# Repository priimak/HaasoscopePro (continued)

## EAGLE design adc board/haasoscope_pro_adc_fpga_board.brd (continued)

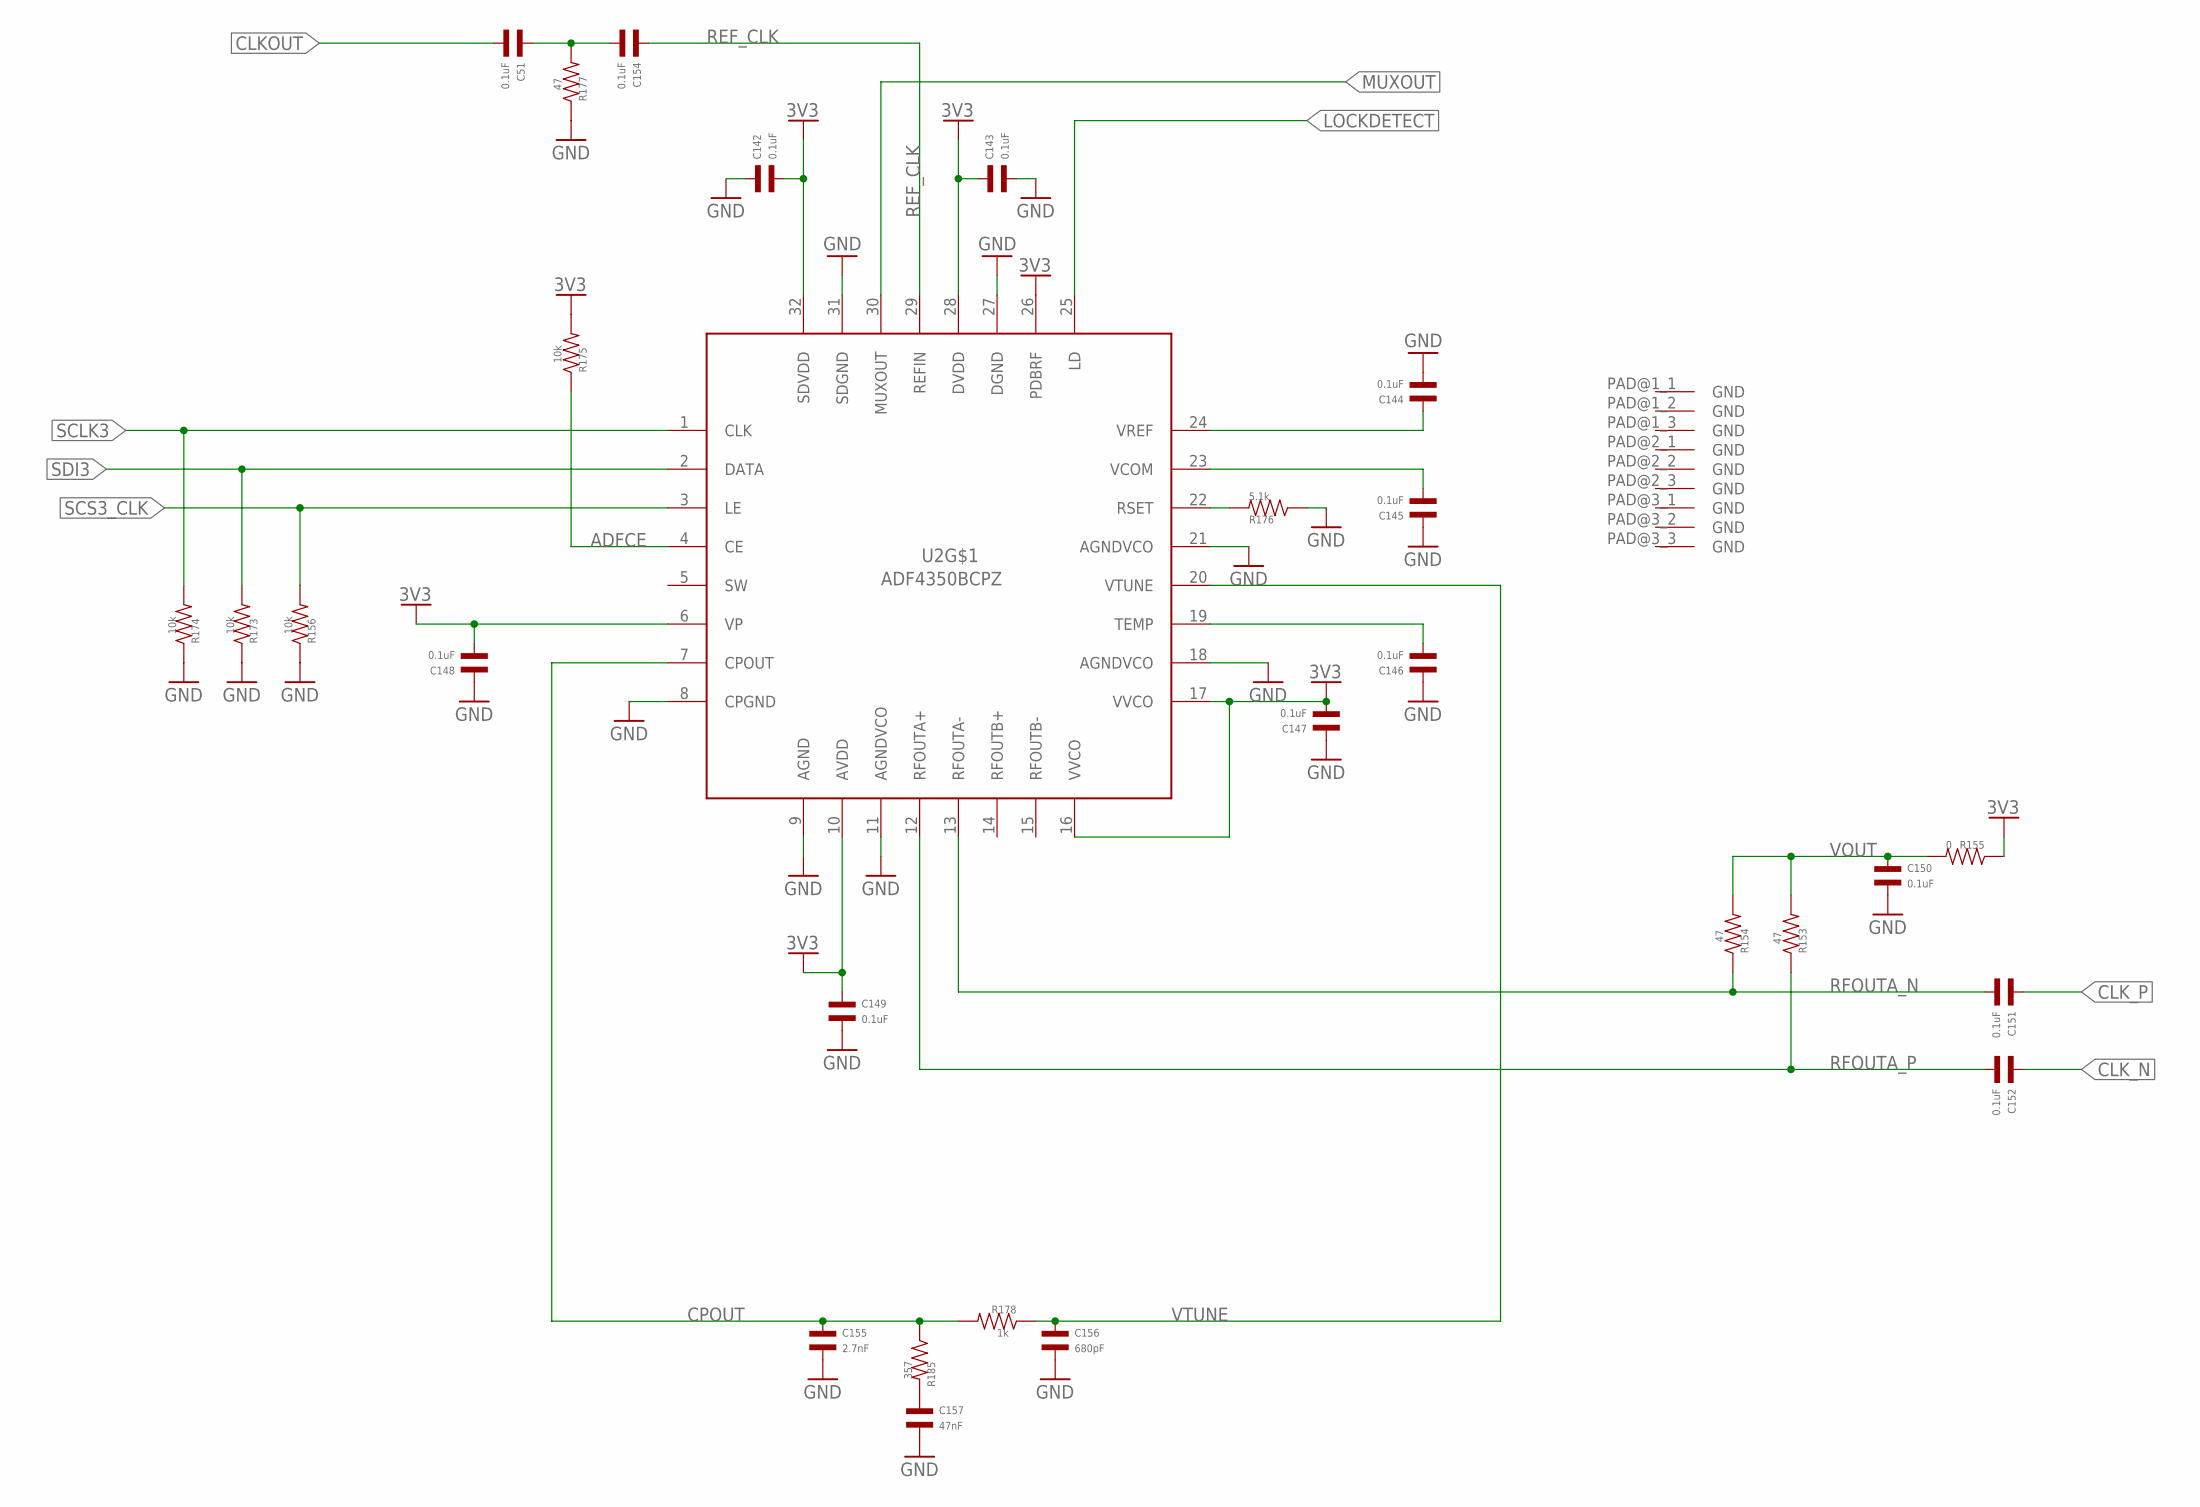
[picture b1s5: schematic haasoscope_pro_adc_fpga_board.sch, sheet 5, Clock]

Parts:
C51, C142, C143, C144, C145, C146, C147, C148, C149, C150, C151, C152, C154: 0.1uF; C0402
C155: 2.7nF; C0402
C156: 680pF; C0402
C157: 47nF; C0402
R153, R154, R177: 47; R0402
R155: 0; R0402
R156, R173, R174, R175: 10k; R0402
R176: 5.1k; R0402
R178: 1k; R0402
R185: 357; R0402
U2: ADF4350BCPZ; QFN50P500X500X100-33V2N

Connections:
3V3: C142.P$2, C143.P$1, C147.P$2, C148.P$2, C149.P$1, R155.P$1, R175.P$2, U2.6 (VP), U2.10 (AVDD), U2.16 (VVCO), U2.17 (VVCO), U2.26 (PDBRF), U2.28 (DVDD), U2.32 (SDVDD); also elsewhere on the board
ADFCE: R175.P$1, U2.4 (CE)
CLKOUT: C51.P$2; also elsewhere on the board
CLKOUTAC: C51.P$1, C154.P$2, R177.P$2
CLK_N: C152.P$1; also elsewhere on the board
CLK_P: C151.P$1; also elsewhere on the board
CPOUT: C155.P$1, R178.P$2, R185.P$1, U2.7 (CPOUT)
GND: C142.P$1, C143.P$2, C144.P$2, C145.P$1, C146.P$1, C147.P$1, C148.P$1, C149.P$2, C150.P$2, C155.P$2, C156.P$2, C157.P$2, R156.P$1, R173.P$1, R174.P$1, R176.P$1, R177.P$1, U2.8 (CPGND), U2.9 (AGND), U2.11 (AGNDVCO), U2.18 (AGNDVCO), U2.21 (AGNDVCO), U2.27 (DGND), U2.31 (SDGND), U2.PAD@1_1 (GND), U2.PAD@1_2 (GND), U2.PAD@1_3 (GND), U2.PAD@2_1 (GND), U2.PAD@2_2 (GND), U2.PAD@2_3 (GND), U2.PAD@3_1 (GND), U2.PAD@3_2 (GND), U2.PAD@3_3 (GND); also elsewhere on the board
LOCKDETECT: U2.25 (LD); also elsewhere on the board
MUXOUT: U2.30 (MUXOUT); also elsewhere on the board
unnamed: C146.P$2, U2.19 (TEMP)
unnamed: C145.P$2, U2.23 (VCOM)
unnamed: R176.P$2, U2.22 (RSET)
unnamed: C157.P$1, R185.P$2
REF_CLK: C154.P$1, U2.29 (REFIN)
RFOUTA_N: C151.P$2, R154.P$1, U2.13 (RFOUTA-)
RFOUTA_P: C152.P$2, R153.P$1, U2.12 (RFOUTA+)
SCLK3: R174.P$2, U2.1 (CLK); also elsewhere on the board
SCS3_CLK: R156.P$2, U2.3 (LE); also elsewhere on the board
SDI3: R173.P$2, U2.2 (DATA); also elsewhere on the board
VOUT: C150.P$1, R153.P$2, R154.P$2, R155.P$2
VREF2: C144.P$1, U2.24 (VREF)
VTUNE: C156.P$1, R178.P$1, U2.20 (VTUNE)

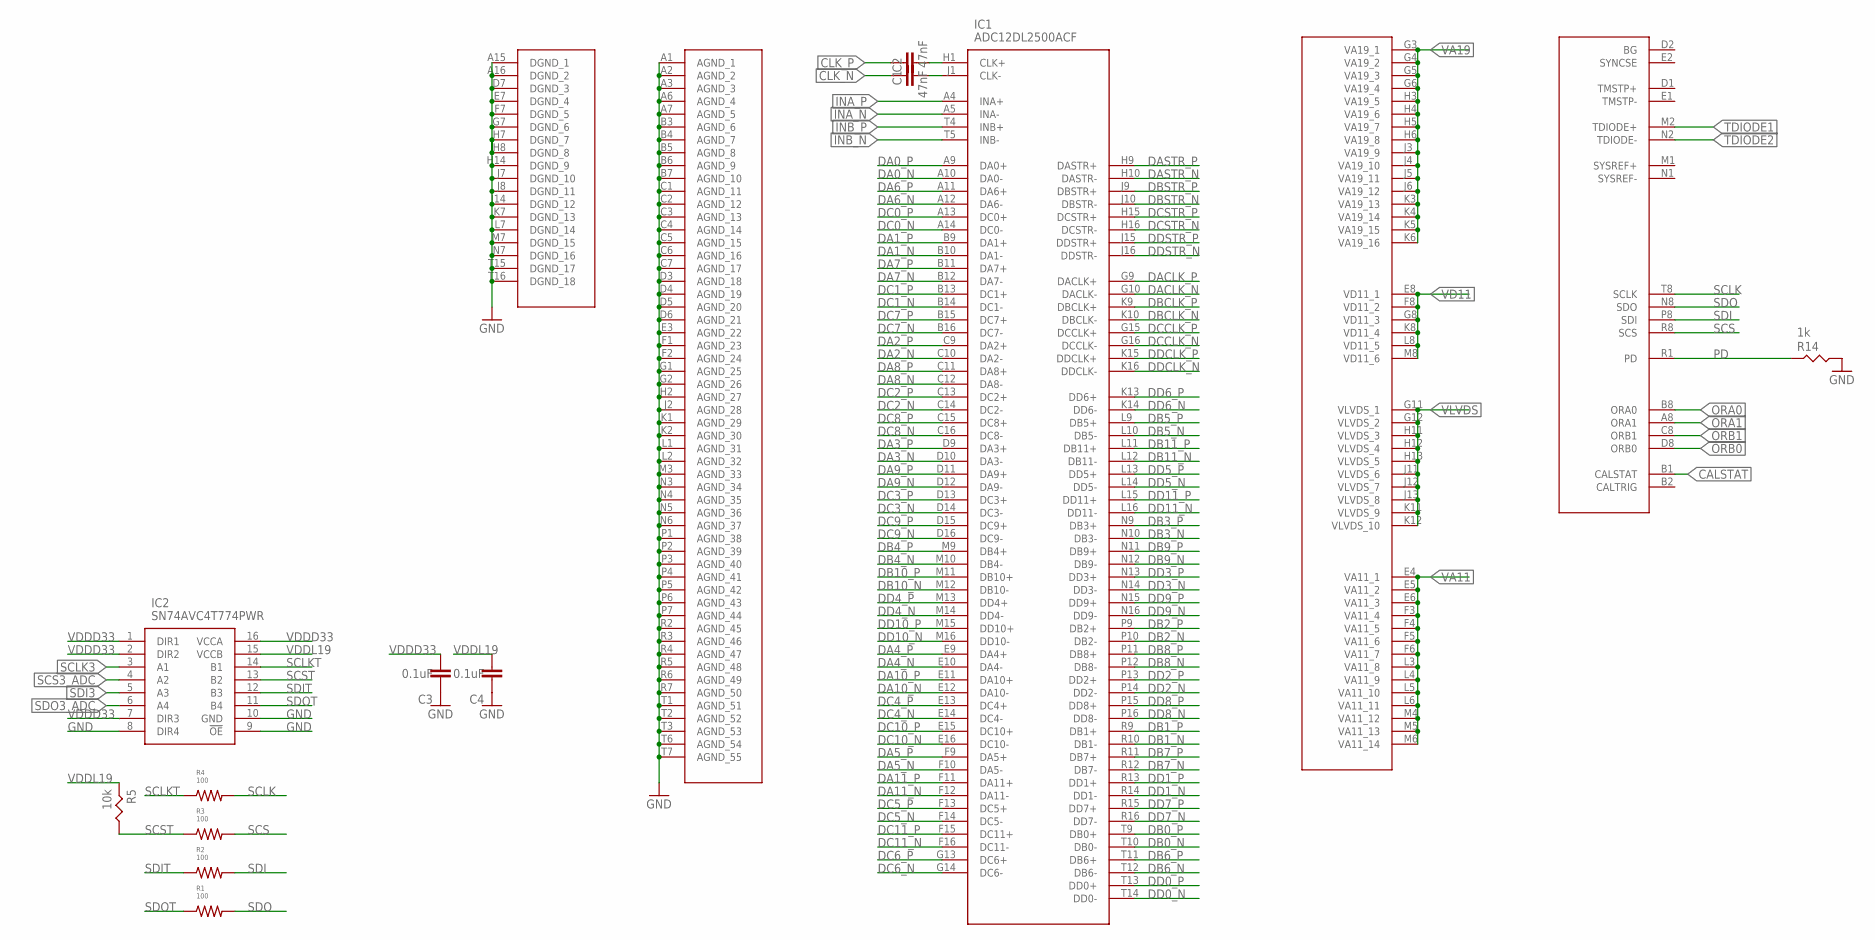
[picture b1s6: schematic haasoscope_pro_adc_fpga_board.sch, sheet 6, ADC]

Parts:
C1, C2: 47nF; RESC0402_N
C3, C4: 0.1uF; RESC0402_N
IC1: ADC12DL2500ACF; BGA256C100P16X16_1700X1700X331; MANUFACTURER_PART_NUMBER ADC12DL500ACF
IC2: SN74AVC4T774PWR; SOP65P640X120-16N
R1, R2, R3, R4: 100; R0201
R5: 10k; RES-0402
R14: 1k; RES-0402

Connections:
CALSTAT: IC1.B1 (CALSTAT); also elsewhere on the board
CLK_AC_N: C1.1, IC1.J1 (CLK-)
CLK_AC_P: C2.2, IC1.H1 (CLK+)
CLK_N: C1.2; also elsewhere on the board
CLK_P: C2.1; also elsewhere on the board
DA0_N: IC1.A10 (DA0-); also elsewhere on the board
DA0_P: IC1.A9 (DA0+); also elsewhere on the board
DA1_N: IC1.B10 (DA1-); also elsewhere on the board
DA1_P: IC1.B9 (DA1+); also elsewhere on the board
DA2_N: IC1.C10 (DA2-); also elsewhere on the board
DA2_P: IC1.C9 (DA2+); also elsewhere on the board
DA3_N: IC1.D10 (DA3-); also elsewhere on the board
DA3_P: IC1.D9 (DA3+); also elsewhere on the board
DA4_N: IC1.E10 (DA4-); also elsewhere on the board
DA4_P: IC1.E9 (DA4+); also elsewhere on the board
DA5_N: IC1.F10 (DA5-); also elsewhere on the board
DA5_P: IC1.F9 (DA5+); also elsewhere on the board
DA6_N: IC1.A12 (DA6-); also elsewhere on the board
DA6_P: IC1.A11 (DA6+); also elsewhere on the board
DA7_N: IC1.B12 (DA7-); also elsewhere on the board
DA7_P: IC1.B11 (DA7+); also elsewhere on the board
DA8_N: IC1.C12 (DA8-); also elsewhere on the board
DA8_P: IC1.C11 (DA8+); also elsewhere on the board
DA9_N: IC1.D12 (DA9-); also elsewhere on the board
DA9_P: IC1.D11 (DA9+); also elsewhere on the board
DA10_N: IC1.E12 (DA10-); also elsewhere on the board
DA10_P: IC1.E11 (DA10+); also elsewhere on the board
DA11_N: IC1.F12 (DA11-); also elsewhere on the board
DA11_P: IC1.F11 (DA11+); also elsewhere on the board
DACLK_N: IC1.G10 (DACLK-); also elsewhere on the board
DACLK_P: IC1.G9 (DACLK+); also elsewhere on the board
DASTR_N: IC1.H10 (DASTR-); also elsewhere on the board
DASTR_P: IC1.H9 (DASTR+); also elsewhere on the board
DB0_N: IC1.T10 (DB0-); also elsewhere on the board
DB0_P: IC1.T9 (DB0+); also elsewhere on the board
DB1_N: IC1.R10 (DB1-); also elsewhere on the board
DB1_P: IC1.R9 (DB1+); also elsewhere on the board
DB2_N: IC1.P10 (DB2-); also elsewhere on the board
DB2_P: IC1.P9 (DB2+); also elsewhere on the board
DB3_N: IC1.N10 (DB3-); also elsewhere on the board
DB3_P: IC1.N9 (DB3+); also elsewhere on the board
DB4_N: IC1.M10 (DB4-); also elsewhere on the board
DB4_P: IC1.M9 (DB4+); also elsewhere on the board
DB5_N: IC1.L10 (DB5-); also elsewhere on the board
DB5_P: IC1.L9 (DB5+); also elsewhere on the board
DB6_N: IC1.T12 (DB6-); also elsewhere on the board
DB6_P: IC1.T11 (DB6+); also elsewhere on the board
DB7_N: IC1.R12 (DB7-); also elsewhere on the board
DB7_P: IC1.R11 (DB7+); also elsewhere on the board
DB8_N: IC1.P12 (DB8-); also elsewhere on the board
DB8_P: IC1.P11 (DB8+); also elsewhere on the board
DB9_N: IC1.N12 (DB9-); also elsewhere on the board
DB9_P: IC1.N11 (DB9+); also elsewhere on the board
DB10_N: IC1.M12 (DB10-); also elsewhere on the board
DB10_P: IC1.M11 (DB10+); also elsewhere on the board
DB11_N: IC1.L12 (DB11-); also elsewhere on the board
DB11_P: IC1.L11 (DB11+); also elsewhere on the board
DBCLK_N: IC1.K10 (DBCLK-); also elsewhere on the board
DBCLK_P: IC1.K9 (DBCLK+); also elsewhere on the board
DBSTR_N: IC1.J10 (DBSTR-); also elsewhere on the board
DBSTR_P: IC1.J9 (DBSTR+); also elsewhere on the board
DC0_N: IC1.A14 (DC0-); also elsewhere on the board
DC0_P: IC1.A13 (DC0+); also elsewhere on the board
DC1_N: IC1.B14 (DC1-); also elsewhere on the board
DC1_P: IC1.B13 (DC1+); also elsewhere on the board
DC2_N: IC1.C14 (DC2-); also elsewhere on the board
DC2_P: IC1.C13 (DC2+); also elsewhere on the board
DC3_N: IC1.D14 (DC3-); also elsewhere on the board
DC3_P: IC1.D13 (DC3+); also elsewhere on the board
DC4_N: IC1.E14 (DC4-); also elsewhere on the board
DC4_P: IC1.E13 (DC4+); also elsewhere on the board
DC5_N: IC1.F14 (DC5-); also elsewhere on the board
DC5_P: IC1.F13 (DC5+); also elsewhere on the board
DC6_N: IC1.G14 (DC6-); also elsewhere on the board
DC6_P: IC1.G13 (DC6+); also elsewhere on the board
DC7_N: IC1.B16 (DC7-); also elsewhere on the board
DC7_P: IC1.B15 (DC7+); also elsewhere on the board
DC8_N: IC1.C16 (DC8-); also elsewhere on the board
DC8_P: IC1.C15 (DC8+); also elsewhere on the board
DC9_N: IC1.D16 (DC9-); also elsewhere on the board
DC9_P: IC1.D15 (DC9+); also elsewhere on the board
DC10_N: IC1.E16 (DC10-); also elsewhere on the board
DC10_P: IC1.E15 (DC10+); also elsewhere on the board
DC11_N: IC1.F16 (DC11-); also elsewhere on the board
DC11_P: IC1.F15 (DC11+); also elsewhere on the board
DCCLK_N: IC1.G16 (DCCLK-); also elsewhere on the board
DCCLK_P: IC1.G15 (DCCLK+); also elsewhere on the board
DCSTR_N: IC1.H16 (DCSTR-); also elsewhere on the board
DCSTR_P: IC1.H15 (DCSTR+); also elsewhere on the board
DD0_N: IC1.T14 (DD0-); also elsewhere on the board
DD0_P: IC1.T13 (DD0+); also elsewhere on the board
DD1_N: IC1.R14 (DD1-); also elsewhere on the board
DD1_P: IC1.R13 (DD1+); also elsewhere on the board
DD2_N: IC1.P14 (DD2-); also elsewhere on the board
DD2_P: IC1.P13 (DD2+); also elsewhere on the board
DD3_N: IC1.N14 (DD3-); also elsewhere on the board
DD3_P: IC1.N13 (DD3+); also elsewhere on the board
DD4_N: IC1.M14 (DD4-); also elsewhere on the board
DD4_P: IC1.M13 (DD4+); also elsewhere on the board
DD5_N: IC1.L14 (DD5-); also elsewhere on the board
DD5_P: IC1.L13 (DD5+); also elsewhere on the board
DD6_N: IC1.K14 (DD6-); also elsewhere on the board
DD6_P: IC1.K13 (DD6+); also elsewhere on the board
DD7_N: IC1.R16 (DD7-); also elsewhere on the board
DD7_P: IC1.R15 (DD7+); also elsewhere on the board
DD8_N: IC1.P16 (DD8-); also elsewhere on the board
DD8_P: IC1.P15 (DD8+); also elsewhere on the board
DD9_N: IC1.N16 (DD9-); also elsewhere on the board
DD9_P: IC1.N15 (DD9+); also elsewhere on the board
DD10_N: IC1.M16 (DD10-); also elsewhere on the board
DD10_P: IC1.M15 (DD10+); also elsewhere on the board
DD11_N: IC1.L16 (DD11-); also elsewhere on the board
DD11_P: IC1.L15 (DD11+); also elsewhere on the board
DDCLK_N: IC1.K16 (DDCLK-); also elsewhere on the board
DDCLK_P: IC1.K15 (DDCLK+); also elsewhere on the board
DDSTR_N: IC1.J16 (DDSTR-); also elsewhere on the board
DDSTR_P: IC1.J15 (DDSTR+); also elsewhere on the board
GND: C3.1, C4.1, IC1.A1 (AGND_1), IC1.A2 (AGND_2), IC1.A3 (AGND_3), IC1.A6 (AGND_4), IC1.A7 (AGND_5), IC1.A15 (DGND_1), IC1.A16 (DGND_2), IC1.B3 (AGND_6), IC1.B4 (AGND_7), IC1.B5 (AGND_8), IC1.B6 (AGND_9), IC1.B7 (AGND_10), IC1.C1 (AGND_11), IC1.C2 (AGND_12), IC1.C3 (AGND_13), IC1.C4 (AGND_14), IC1.C5 (AGND_15), IC1.C6 (AGND_16), IC1.C7 (AGND_17), IC1.D3 (AGND_18), IC1.D4 (AGND_19), IC1.D5 (AGND_20), IC1.D6 (AGND_21), IC1.D7 (DGND_3), IC1.E3 (AGND_22), IC1.E7 (DGND_4), IC1.F1 (AGND_23), IC1.F2 (AGND_24), IC1.F7 (DGND_5), IC1.G1 (AGND_25), IC1.G2 (AGND_26), IC1.G7 (DGND_6), IC1.H2 (AGND_27), IC1.H7 (DGND_7), IC1.H8 (DGND_8), IC1.H14 (DGND_9), IC1.J2 (AGND_28), IC1.J7 (DGND_10), IC1.J8 (DGND_11), IC1.J14 (DGND_12), IC1.K1 (AGND_29), IC1.K2 (AGND_30), IC1.K7 (DGND_13), IC1.L1 (AGND_31), IC1.L2 (AGND_32), IC1.L7 (DGND_14), IC1.M3 (AGND_33), IC1.M7 (DGND_15), IC1.N3 (AGND_34), IC1.N4 (AGND_35), IC1.N5 (AGND_36), IC1.N6 (AGND_37), IC1.N7 (DGND_16), IC1.P1 (AGND_38), IC1.P2 (AGND_39), IC1.P3 (AGND_40), IC1.P4 (AGND_41), IC1.P5 (AGND_42), IC1.P6 (AGND_43), IC1.P7 (AGND_44), IC1.R2 (AGND_45), IC1.R3 (AGND_46), IC1.R4 (AGND_47), IC1.R5 (AGND_48), IC1.R6 (AGND_49), IC1.R7 (AGND_50), IC1.T1 (AGND_51), IC1.T2 (AGND_52), IC1.T3 (AGND_53), IC1.T6 (AGND_54), IC1.T7 (AGND_55), IC1.T15 (DGND_17), IC1.T16 (DGND_18), IC2.8 (DIR4), IC2.9 (!OE), IC2.10 (GND), R14.P$2; also elsewhere on the board
INA_N: IC1.A5 (INA-); also elsewhere on the board
INA_P: IC1.A4 (INA+); also elsewhere on the board
INB_N: IC1.T5 (INB-); also elsewhere on the board
INB_P: IC1.T4 (INB+); also elsewhere on the board
ORA0: IC1.B8 (ORA0); also elsewhere on the board
ORA1: IC1.A8 (ORA1); also elsewhere on the board
ORB0: IC1.D8 (ORB0); also elsewhere on the board
ORB1: IC1.C8 (ORB1); also elsewhere on the board
PD: IC1.R1 (PD), R14.P$1
SCLK: IC1.T8 (SCLK), R4.2
SCLK3: IC2.3 (A1); also elsewhere on the board
SCLKT: IC2.14 (B1), R4.1
SCS: IC1.R8 (SCS), R3.2
SCS3_ADC: IC2.4 (A2); also elsewhere on the board
SCST: IC2.13 (B2), R3.1, R5.P$2
SDI: IC1.P8 (SDI), R2.2
SDI3: IC2.5 (A3); also elsewhere on the board
SDIT: IC2.12 (B3), R2.1
SDO: IC1.N8 (SDO), R1.2
SDO3_ADC: IC2.6 (A4); also elsewhere on the board
SDOT: IC2.11 (B4), R1.1
TDIODE1: IC1.M2 (TDIODE+); also elsewhere on the board
TDIODE2: IC1.N2 (TDIODE-); also elsewhere on the board
VA11: IC1.E4 (VA11_1), IC1.E5 (VA11_2), IC1.E6 (VA11_3), IC1.F3 (VA11_4), IC1.F4 (VA11_5), IC1.F5 (VA11_6), IC1.F6 (VA11_7), IC1.L3 (VA11_8), IC1.L4 (VA11_9), IC1.L5 (VA11_10), IC1.L6 (VA11_11), IC1.M4 (VA11_12), IC1.M5 (VA11_13), IC1.M6 (VA11_14); also elsewhere on the board
VA19: IC1.G3 (VA19_1), IC1.G4 (VA19_2), IC1.G5 (VA19_3), IC1.G6 (VA19_4), IC1.H3 (VA19_5), IC1.H4 (VA19_6), IC1.H5 (VA19_7), IC1.H6 (VA19_8), IC1.J3 (VA19_9), IC1.J4 (VA19_10), IC1.J5 (VA19_11), IC1.J6 (VA19_12), IC1.K3 (VA19_13), IC1.K4 (VA19_14), IC1.K5 (VA19_15), IC1.K6 (VA19_16); also elsewhere on the board
VD11: IC1.E8 (VD11_1), IC1.F8 (VD11_2), IC1.G8 (VD11_3), IC1.K8 (VD11_4), IC1.L8 (VD11_5), IC1.M8 (VD11_6); also elsewhere on the board
VDDD33: C3.2, IC2.1 (DIR1), IC2.2 (DIR2), IC2.7 (DIR3), IC2.16 (VCCA); also elsewhere on the board
VDDL19: C4.2, IC2.15 (VCCB), R5.P$1; also elsewhere on the board
VLVDS: IC1.G11 (VLVDS_1), IC1.G12 (VLVDS_2), IC1.H11 (VLVDS_3), IC1.H12 (VLVDS_4), IC1.H13 (VLVDS_5), IC1.J11 (VLVDS_6), IC1.J12 (VLVDS_7), IC1.J13 (VLVDS_8), IC1.K11 (VLVDS_9), IC1.K12 (VLVDS_10); also elsewhere on the board
